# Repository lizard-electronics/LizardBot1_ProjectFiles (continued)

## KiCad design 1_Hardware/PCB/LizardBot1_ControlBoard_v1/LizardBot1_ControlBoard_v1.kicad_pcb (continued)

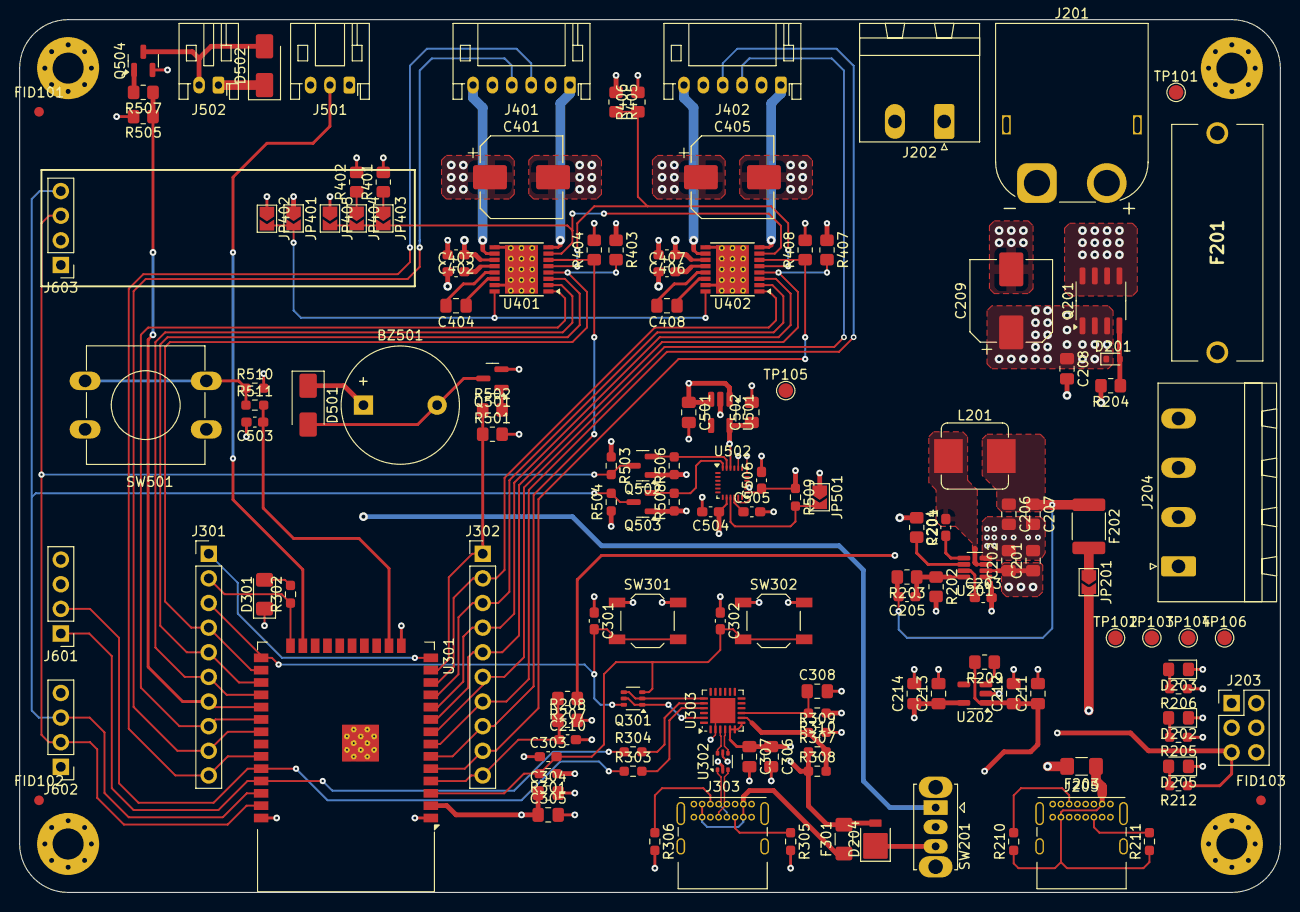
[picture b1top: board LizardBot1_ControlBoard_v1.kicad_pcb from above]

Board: 4 copper layers, 130.0 x 90.0 mm, 145 parts (0 on the bottom side), 92 nets.

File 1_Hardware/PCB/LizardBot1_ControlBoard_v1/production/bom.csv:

Designator,Footprint,Quantity,Value,LCSC Part #
BZ501,Buzzer_12x9.5RM7.6,1,Buzzer,
"C201, C206, C207, C208, C304",0805,5,22uF,
"C202, C212, C305, C307, C308",0805,5,0.1uF,
"C203, C204, C210, C301, C302, C303, C402, C403, C406, C407, C503, C504, C505, C506",0603,14,0.1uF,
C205,0603,1,33pF,
C209,CP_Elec_8x10,1,470uF,
"C211, C213, C214, C306, C501, C502",0805,6,4.7uF,
"C401, C405",CP_Elec_8x10,2,220uF,
"C404, C408",0805,2,22nF,
D201,D_SOD-523,1,BZT52C12T,
"D202, D203, D205",0805,3,Green,
D204,D_SMP_DO-220AA,1,SS1P3L,
D301,1206,1,Red,
"D501, D502",D_SMA,2,SS14,
F201,Fuseholder_LittelFuse_5x20mm_0PTF0078P,1,10A,
F202,1812,1,5A,
F203,1206,1,3A,
F301,1206,1,500mA,
J201,AMASS_XT60PW-M_1x02_P7.20mm_Horizontal,1,XT60-M,
J202,"PhoenixContact_MSTBA_2,5_2-G-5,08_1x02_P5.08mm_Horizontal",1,Receptable-P5.08-2P,
J203,PinHeader_2x03_P2.54mm_Vertical,1,Conn_02x03_Odd_Even,
J204,"PhoenixContact_MSTBA_2,5_4-G-5,08_1x04_P5.08mm_Horizontal",1,Receptable-P5.08-4P,
J205,USB_C_Receptacle_GCT_USB4085,1,USB_C_Receptacle_PowerOnly_6P,
"J301, J302",PinHeader_1x10_P2.54mm_Vertical,2,2.54mm (F),
J303,USB_C_Receptacle_GCT_USB4085,1,USB_C_Receptacle_USB2.0_16P,
"J401, J402",JST_PH_S6B-PH-K_1x06_P2.00mm_Horizontal,2,JST-PH-6-Male,
J501,JST_PH_S3B-PH-K_1x03_P2.00mm_Horizontal,1,JST-PH-3-Male,
J502,JST_PH_S2B-PH-K_1x02_P2.00mm_Horizontal,1,JST-PH-2-Male,
"J601, J602, J603",PinHeader_1x04_P2.54mm_Vertical,3,2.54mm (F),
L201,L_Bourns_SRP7028A_7.3x6.6mm,1,4.7uH,
Q201,SO-8_3.9x4.9mm_P1.27mm,1,SQ4425EY,
Q301,SOT-363_SC-70-6,1,UMH3N,
"Q501, Q504",SOT-23,2,AO3400A,
"Q502, Q503",SOT-23,2,BSS138,
"R201, R209",0805,2,100k,
R202,0805,1,5.49k,
R203,0805,1,40.2k,
"R204, R207, R403, R407, R501, R505",0805,6,10k,
"R205, R206, R302, R310",0603,4,1k,
R208,0805,1,3.3k,
"R210, R211, R301, R503, R504, R506, R508, R509, R510",0603,9,10k,
"R212, R511",0603,2,470,
"R303, R304",0603,2,0,
"R305, R306",0603,2,5k1,
"R307, R308, R309",0603,3,47k,
R401,0805,1,62k,
R402,0805,1,20k,
"R404, R408",0805,2,1.2k,
R405,0805,1,16k,
R406,0805,1,50k,
"R502, R507",0805,2,150,
SW201,SW_Slide_SPDT_Straight_CK_OS102011MS2Q,1,SW_SPDT,
"SW301, SW302",SW_SPST_TL3342,2,SW_Push,
SW501,SW_PUSH-12mm,1,SW_Push,
U201,SOT-23-8,1,MP2225,
U202,SOT-23-5,1,AP2112K-3.3,
U301,ESP32-WROOM-32D,1,ESP32-WROOM-32E,
U302,SOT-666,1,USBLC6-2P6,
U303,QFN-24-1EP_4x4mm_P0.5mm_EP2.6x2.6mm,1,CP2102N-Axx-xQFN24,
"U401, U402",HTSSOP-16-1EP_4.4x5mm_P0.65mm_EP3.4x5mm_Mask3x3mm_ThermalVias,2,DRV8874,
U501,SOT-23-5_HandSoldering,1,MIC5225,
U502,InvenSense_QFN-24_3x3mm_P0.4mm,1,ICM-20948,

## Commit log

2024-04-12 Added diagrams file to 4_Docs
2024-04-20 Added 1_Hardware files
2024-06-19 Updated Electrical Layout Block Diagram. Added Power_Supply schematic last changes.
2024-06-25 Added Motor_Driver schematic.
2024-07-02 Added MCU schematic
2024-07-03 Added Peripherals schematic
2024-07-04 Added Communication_Interfaces schematic
2024-07-08 PCB schematics revision
2024-07-09 Updated schematics. Assigned footprints. Added BOM to /4_Docs.
2024-07-15 Added PCB Stack and Design Rules. Added PCB Layout file.
2024-07-31 Finished PCB routing. Updated ESP32 GPIO layout.
2024-08-09 Finished robot controller PCB. Generated production files.
2024-08-15 Added PCB 3D model & PCB layer view files.
2024-08-27 Updated BOM.
2024-09-06 Added ControlBoard firmware to test motor drivers.
2024-09-07 Edited files.
2024-09-09 Started Control Board firmware development.
2024-09-18 Finished and tested ControlBoard firmware.
